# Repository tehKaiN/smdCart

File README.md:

# Custom Sega MegaDrive Cartridges

On this repo you will find schematics for SMD carts of various memory size. Each directory is dedicated to cart of given size.

## Current carts

- `512k` - 512 KByte cart based on 27c4001 chip. Home-etching friendly PCB design. Not tested!
- `1m_29f800` - 1 MByte cart based on 29f800 chip. Erasable/programmable using [ROMprg](https://github.com/tehKaiN/ROMprg) project.
- `2m_29f800` - **Untested!** 1-2 MByte cart based on 1-2 29f800 chips. Erasable/programmable using [ROMprg](https://github.com/tehKaiN/ROMprg) project.

## PCB Ordering instructions

MegaDrive carts have thickness of 1.6mm.

## Creating new cart

When designing PCBs for new cart, the most safe way to get proper dimensions is to copy them from other carts. Some notes:

- maximum cart height is about 60mm, otherwise it won't fit the case;
- distance between mechanical holes is 70mm
- mechanical holes should have diameter of about 6,75mm - add about 1mm for electroplating.
- there should be no soldermask around edge connector pins.

After creating new design and checking if it works, you are encouraged to submit pull request to this repo with your design.

## License

I dunno if MPL2.0 fits hardware, but the idea is that you should share your modifications of schematics / board layout.

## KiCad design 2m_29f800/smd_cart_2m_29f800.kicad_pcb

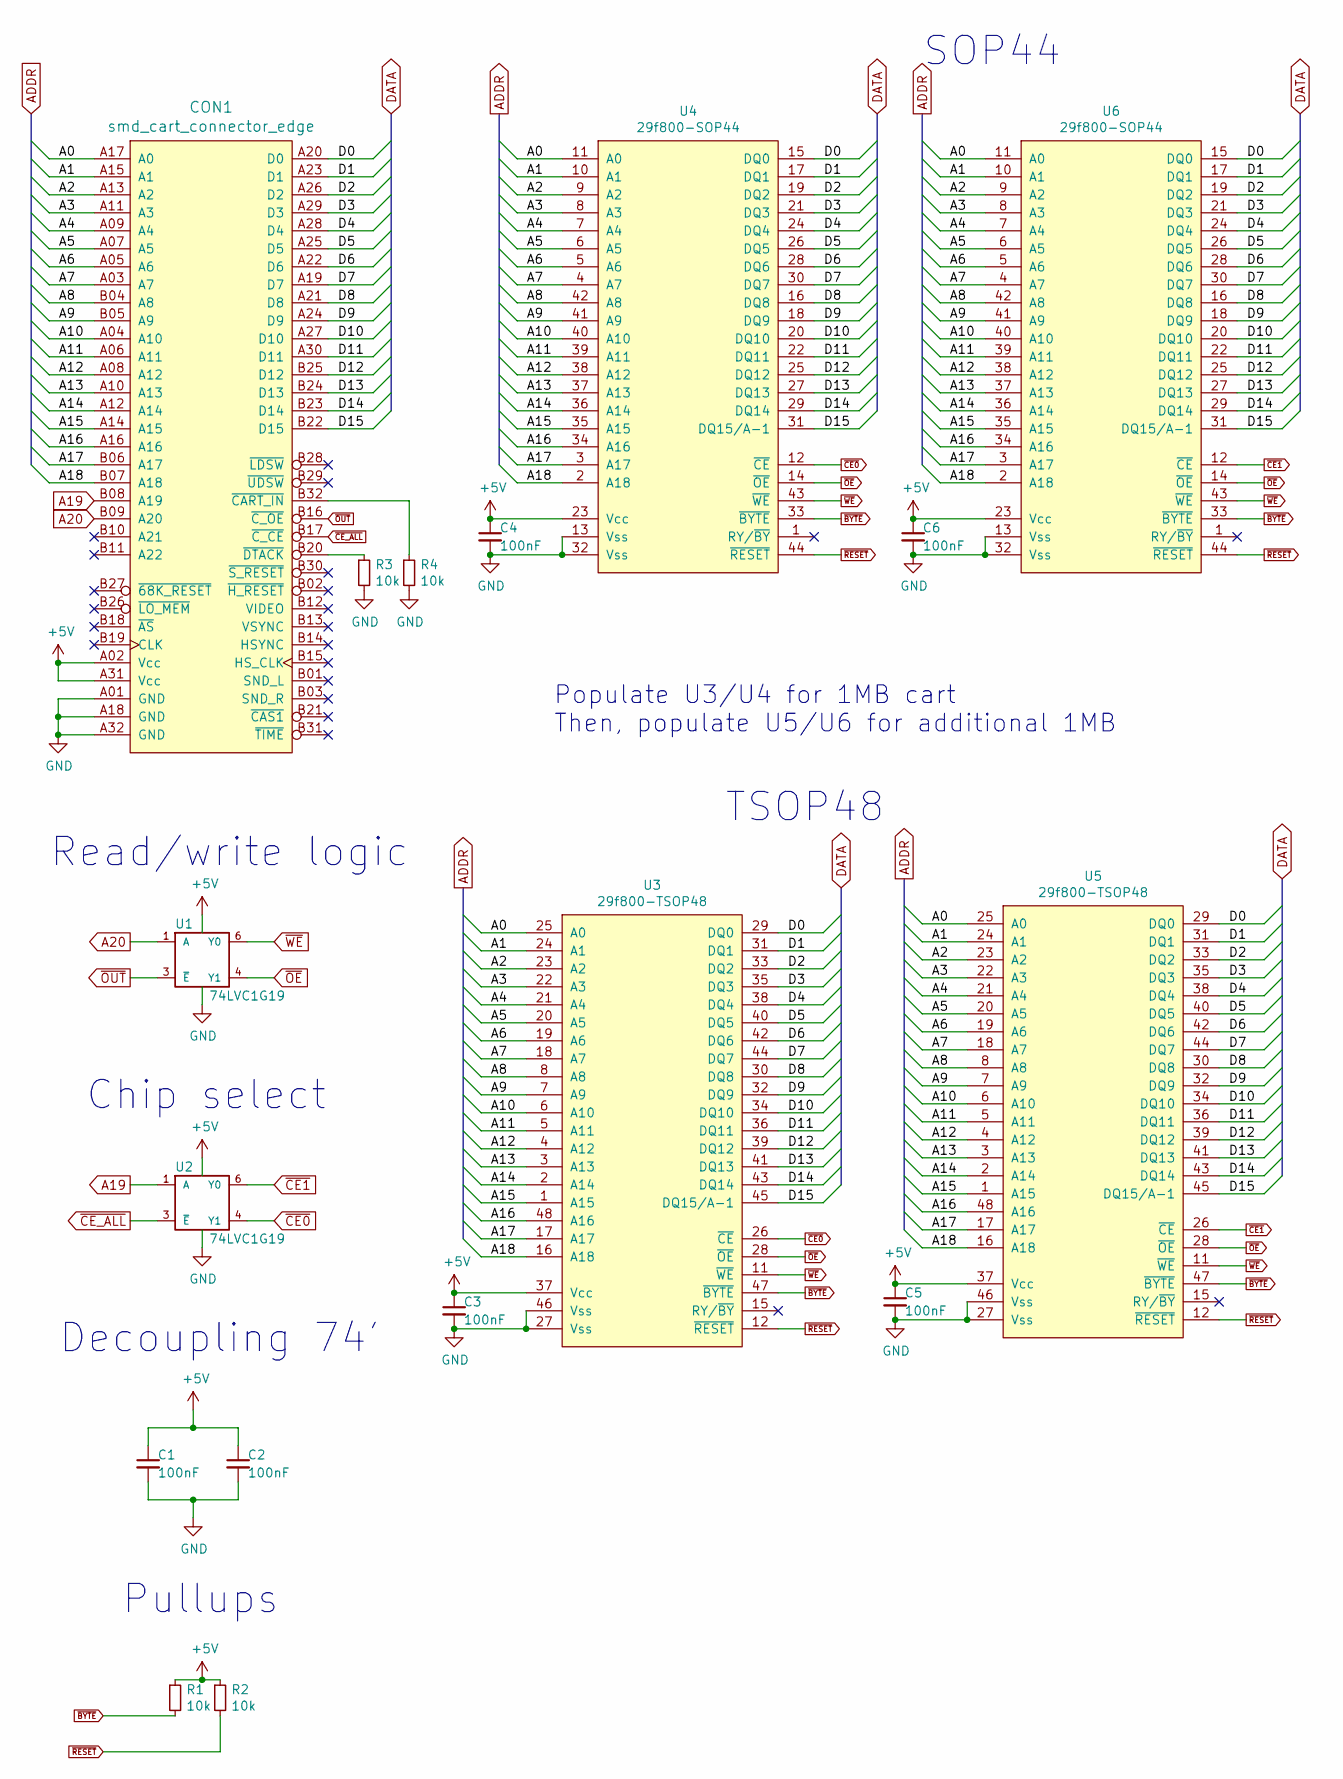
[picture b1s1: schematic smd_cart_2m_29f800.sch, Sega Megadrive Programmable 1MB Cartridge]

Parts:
C1, C2, C3, C4, C5, C6: 100nF; C_0805_2012Metric
CON1: smd_cart_connector_edge; md_cart_edge_conn
R1, R2, R3, R4: 10k; R_0805_2012Metric
U1, U2: 74LVC1G19; SOT-23-6
U3, U5: 29f800-TSOP48; TSOP-I-48_18.4x12mm_P0.5mm
U4, U6: 29f800-SOP44; SOIC-44

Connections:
+5V: C1.1, C2.1, C3.1, C4.1, C5.1, C6.1, CON1.A02 (Vcc), CON1.A31 (Vcc), R1.1, R2.1, U1.5 (VCC), U2.5 (VCC), U3.37 (Vcc), U4.23 (Vcc), U5.37 (Vcc), U6.23 (Vcc)
/A0: CON1.A17 (A0), U3.25 (A0), U4.11 (A0), U5.25 (A0), U6.11 (A0)
/A1: CON1.A15 (A1), U3.24 (A1), U4.10 (A1), U5.24 (A1), U6.10 (A1)
/A2: CON1.A13 (A2), U3.23 (A2), U4.9 (A2), U5.23 (A2), U6.9 (A2)
/A3: CON1.A11 (A3), U3.22 (A3), U4.8 (A3), U5.22 (A3), U6.8 (A3)
/A4: CON1.A09 (A4), U3.21 (A4), U4.7 (A4), U5.21 (A4), U6.7 (A4)
/A5: CON1.A07 (A5), U3.20 (A5), U4.6 (A5), U5.20 (A5), U6.6 (A5)
/A6: CON1.A05 (A6), U3.19 (A6), U4.5 (A6), U5.19 (A6), U6.5 (A6)
/A7: CON1.A03 (A7), U3.18 (A7), U4.4 (A7), U5.18 (A7), U6.4 (A7)
/A8: CON1.B04 (A8), U3.8 (A8), U4.42 (A8), U5.8 (A8), U6.42 (A8)
/A9: CON1.B05 (A9), U3.7 (A9), U4.41 (A9), U5.7 (A9), U6.41 (A9)
/A10: CON1.A04 (A10), U3.6 (A10), U4.40 (A10), U5.6 (A10), U6.40 (A10)
/A11: CON1.A06 (A11), U3.5 (A11), U4.39 (A11), U5.5 (A11), U6.39 (A11)
/A12: CON1.A08 (A12), U3.4 (A12), U4.38 (A12), U5.4 (A12), U6.38 (A12)
/A13: CON1.A10 (A13), U3.3 (A13), U4.37 (A13), U5.3 (A13), U6.37 (A13)
/A14: CON1.A12 (A14), U3.2 (A14), U4.36 (A14), U5.2 (A14), U6.36 (A14)
/A15: CON1.A14 (A15), U3.1 (A15), U4.35 (A15), U5.1 (A15), U6.35 (A15)
/A16: CON1.A16, U3.48 (A16), U4.34 (A16), U5.48 (A16), U6.34 (A16)
/A17: CON1.B06 (A17), U3.17 (A17), U4.3 (A17), U5.17 (A17), U6.3 (A17)
/A18: CON1.B07 (A18), U3.16 (A18), U4.2 (A18), U5.16 (A18), U6.2 (A18)
/D0: CON1.A20 (D0), U3.29 (DQ0), U4.15 (DQ0), U5.29 (DQ0), U6.15 (DQ0)
/D1: CON1.A23 (D1), U3.31 (DQ1), U4.17 (DQ1), U5.31 (DQ1), U6.17 (DQ1)
/D2: CON1.A26 (D2), U3.33 (DQ2), U4.19 (DQ2), U5.33 (DQ2), U6.19 (DQ2)
/D3: CON1.A29 (D3), U3.35 (DQ3), U4.21 (DQ3), U5.35 (DQ3), U6.21 (DQ3)
/D4: CON1.A28 (D4), U3.38 (DQ4), U4.24 (DQ4), U5.38 (DQ4), U6.24 (DQ4)
/D5: CON1.A25 (D5), U3.40 (DQ5), U4.26 (DQ5), U5.40 (DQ5), U6.26 (DQ5)
/D6: CON1.A22 (D6), U3.42 (DQ6), U4.28 (DQ6), U5.42 (DQ6), U6.28 (DQ6)
/D7: CON1.A19 (D7), U3.44 (DQ7), U4.30 (DQ7), U5.44 (DQ7), U6.30 (DQ7)
/D8: CON1.A21 (D8), U3.30 (DQ8), U4.16 (DQ8), U5.30 (DQ8), U6.16 (DQ8)
/D9: CON1.A24 (D9), U3.32 (DQ9), U4.18 (DQ9), U5.32 (DQ9), U6.18 (DQ9)
/D10: CON1.A27 (D10), U3.34 (DQ10), U4.20 (DQ10), U5.34 (DQ10), U6.20 (DQ10)
/D11: CON1.A30 (D11), U3.36 (DQ11), U4.22 (DQ11), U5.36 (DQ11), U6.22 (DQ11)
/D12: CON1.B25 (D12), U3.39 (DQ12), U4.25 (DQ12), U5.39 (DQ12), U6.25 (DQ12)
/D13: CON1.B24 (D13), U3.41 (DQ13), U4.27 (DQ13), U5.41 (DQ13), U6.27 (DQ13)
/D14: CON1.B23 (D14), U3.43 (DQ14), U4.29 (DQ14), U5.43 (DQ14), U6.29 (DQ14)
/D15: CON1.B22 (D15), U3.45 (DQ15/A-1), U4.31 (DQ15/A-1), U5.45 (DQ15/A-1), U6.31 (DQ15/A-1)
A19: CON1.B08 (A19), U2.1 (A)
A20: CON1.B09 (A20), U1.1 (A)
GND: C1.2, C2.2, C3.2, C4.2, C5.2, C6.2, CON1.A01 (GND), CON1.A18 (GND), CON1.A32 (GND), R3.2, R4.2, U1.2 (GND), U2.2 (GND), U3.27 (Vss), U3.46 (Vss), U4.13 (Vss), U4.32 (Vss), U5.27 (Vss), U5.46 (Vss), U6.13 (Vss), U6.32 (Vss)
unnamed: CON1.B20 (~DTACK), R3.1
unnamed: CON1.B32 (~CART_IN), R4.1
~BYTE: R1.2, U3.47 (~BYTE), U4.33 (~BYTE), U5.47 (~BYTE), U6.33 (~BYTE)
~CE0: U2.4 (Y1), U3.26 (~CE), U4.12 (~CE)
~CE1: U2.6 (Y0), U5.26 (~CE), U6.12 (~CE)
~CE_ALL: CON1.B17 (~C_CE), U2.3 (~E)
~OE: U1.4 (Y1), U3.28 (~OE), U4.14 (~OE), U5.28 (~OE), U6.14 (~OE)
~OUT: CON1.B16 (~C_OE), U1.3 (~E)
~RESET: R2.2, U3.12 (~RESET), U4.44 (~RESET), U5.12 (~RESET), U6.44 (~RESET)
~WE: U1.6 (Y0), U3.11 (~WE), U4.43 (~WE), U5.11 (~WE), U6.43 (~WE)

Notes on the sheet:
SOP44
TSOP48
Read/write logic
Decoupling 74'
Chip select
Pullups
Populate U3/U4 for 1MB cart Then, populate U5/U6 for additional 1MB

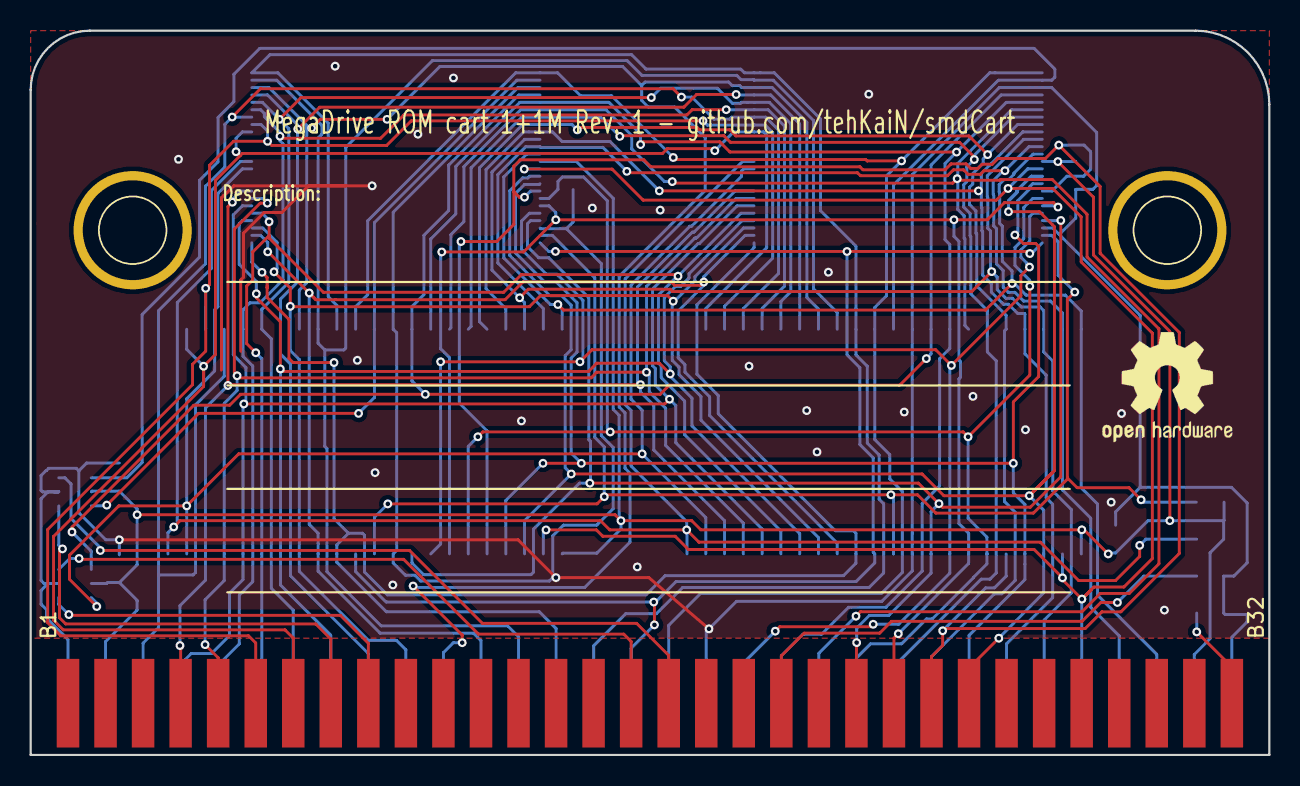
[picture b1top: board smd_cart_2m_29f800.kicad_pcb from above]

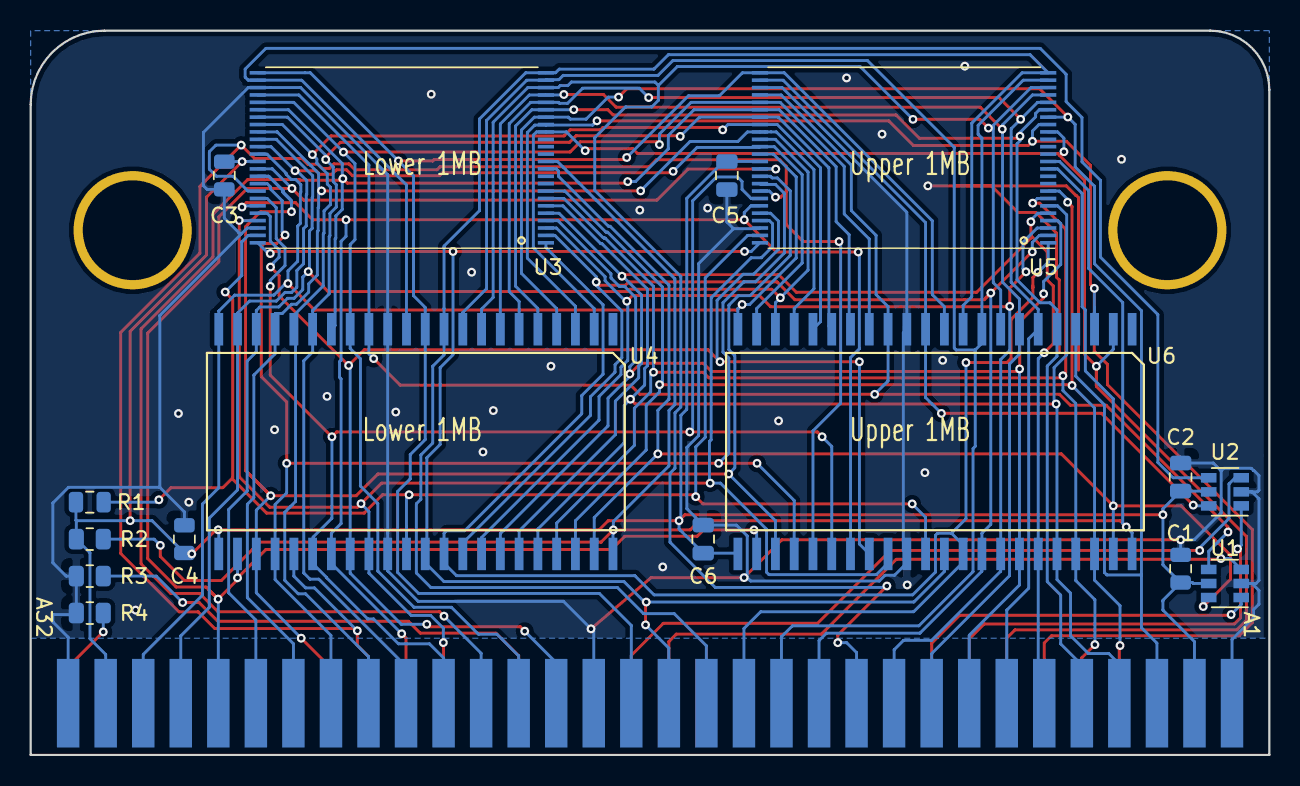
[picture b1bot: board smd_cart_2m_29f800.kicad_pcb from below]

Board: 2 copper layers, 83.8 x 49.0 mm, 19 parts (16 on the bottom side), 49 nets.

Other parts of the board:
DRL1, DRL2: 1pin

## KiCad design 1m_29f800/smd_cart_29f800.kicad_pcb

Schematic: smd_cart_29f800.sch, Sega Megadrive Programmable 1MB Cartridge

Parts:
C1, C2, C3: 100nF; C_0805_2012Metric
CON1: smd_cart_connector_edge; md_cart_edge_conn
R1, R2, R3, R4, R5, R6: 10k; R_0805_2012Metric
U1: 74HCT00; SOIC-14_3.9x8.7mm_P1.27mm
U2: 29f800-TSOP48; TSOP-I-48_18.4x12mm_P0.5mm
U3: 29f800-SOP44; SOIC-44

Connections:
+5V: C1.1, C2.1, C3.1, CON1.A02, CON1.A31, R3.1, R4.1, R5.1, R6.1, U1.14 (VCC), U2.37, U3.23
/A0: CON1.A17, U2.25, U3.11
/A1: CON1.A15, U2.24, U3.10
/A2: CON1.A13, U2.23, U3.9
/A3: CON1.A11, U2.22, U3.8
/A4: CON1.A09, U2.21, U3.7
/A5: CON1.A07, U2.20, U3.6
/A6: CON1.A05, U2.19, U3.5
/A7: CON1.A03, U2.18, U3.4
/A8: CON1.B04, U2.8, U3.42
/A9: CON1.B05, U2.7, U3.41
/A10: CON1.A04, U2.6, U3.40
/A11: CON1.A06, U2.5, U3.39
/A12: CON1.A08, U2.4, U3.38
/A13: CON1.A10, U2.3, U3.37
/A14: CON1.A12, U2.2, U3.36
/A15: CON1.A14, U2.1, U3.35
/A16: CON1.A16, U2.48, U3.34
/A17: CON1.B06, U2.17, U3.3
/A18: CON1.B07, U2.16, U3.2
/D0: CON1.A20, U2.29, U3.15
/D1: CON1.A23, U2.31, U3.17
/D2: CON1.A26, U2.33, U3.19
/D3: CON1.A29, U2.35, U3.21
/D4: CON1.A28, U2.38, U3.24
/D5: CON1.A25, U2.40, U3.26
/D6: CON1.A22, U2.42, U3.28
/D7: CON1.A19, U2.44, U3.30
/D8: CON1.A21, U2.30, U3.16
/D9: CON1.A24, U2.32, U3.18
/D10: CON1.A27, U2.34, U3.20
/D11: CON1.A30, U2.36, U3.22
/D12: CON1.B25, U2.39, U3.25
/D13: CON1.B24, U2.41, U3.27
/D14: CON1.B23, U2.43, U3.29
/D15: CON1.B22, U2.45, U3.31
/OUT: U1.3, U1.5, U1.12
/~A20: U1.8, U1.13
A20: CON1.B09, U1.4, U1.9, U1.10
GND: C1.2, C2.2, C3.2, CON1.A01, CON1.A18, CON1.A32, R1.2, R2.2, U1.7 (GND), U2.27, U2.46, U3.13, U3.32
unnamed: CON1.B20, R1.1
unnamed: CON1.B32, R2.1
unnamed: R3.2, U2.47
unnamed: R4.2, U3.33
unnamed: R5.2, U2.12
unnamed: R6.2, U3.44
~CE: CON1.B17, U2.26, U3.12
~OE: U1.11, U2.28, U3.14
~OUT: CON1.B16, U1.1, U1.2
~WE: U1.6, U2.11, U3.43

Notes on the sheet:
SOP44
TSOP48
Read/write logic
Decoupling

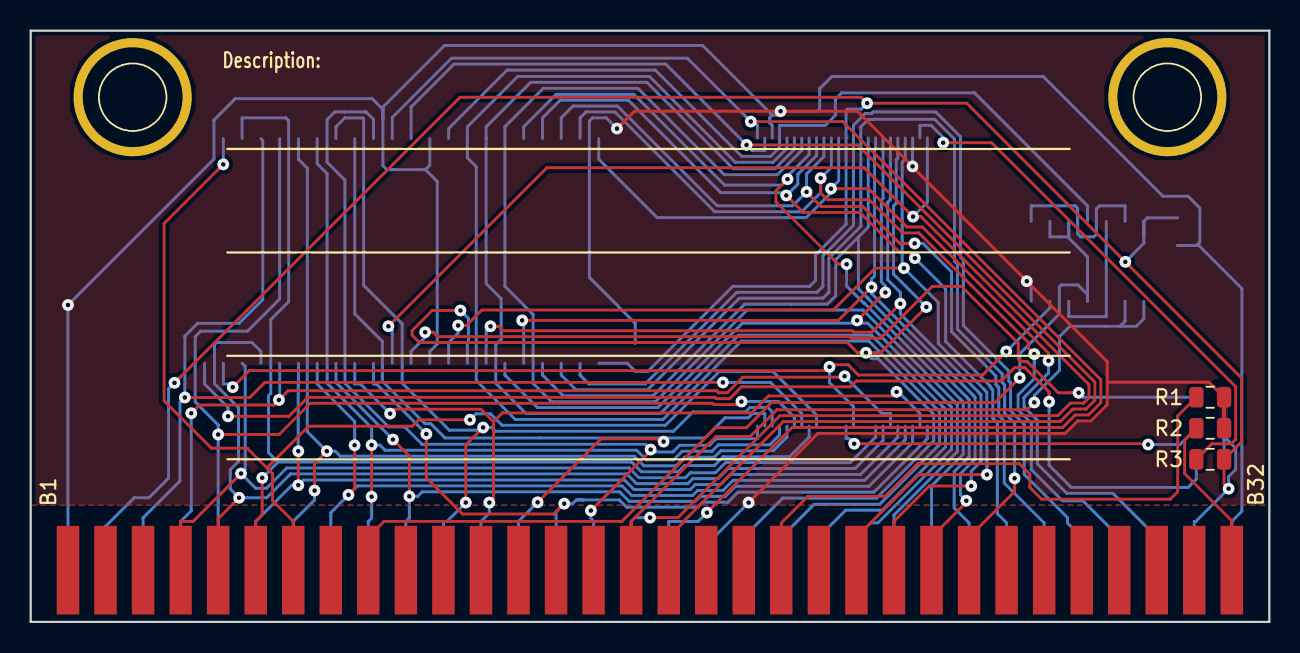
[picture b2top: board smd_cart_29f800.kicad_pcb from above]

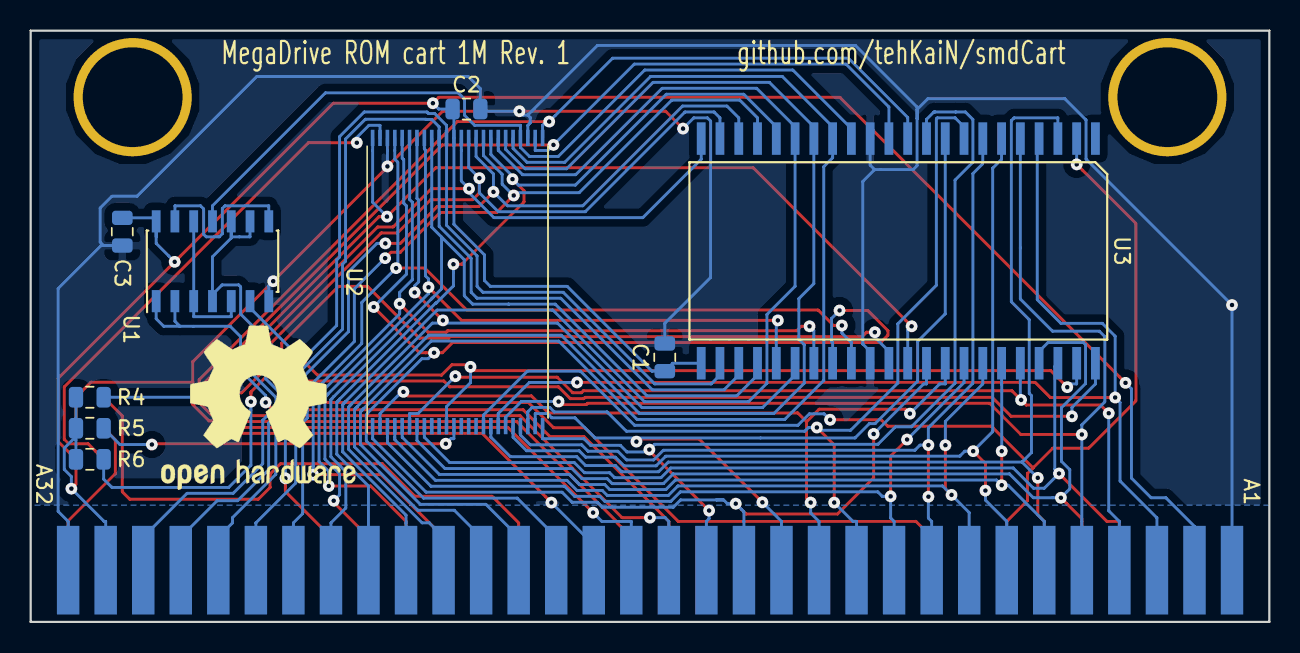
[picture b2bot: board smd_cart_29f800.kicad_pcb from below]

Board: 2 copper layers, 83.8 x 40.0 mm, 15 parts (9 on the bottom side), 50 nets.

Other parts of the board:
DRL1, DRL2: 1pin

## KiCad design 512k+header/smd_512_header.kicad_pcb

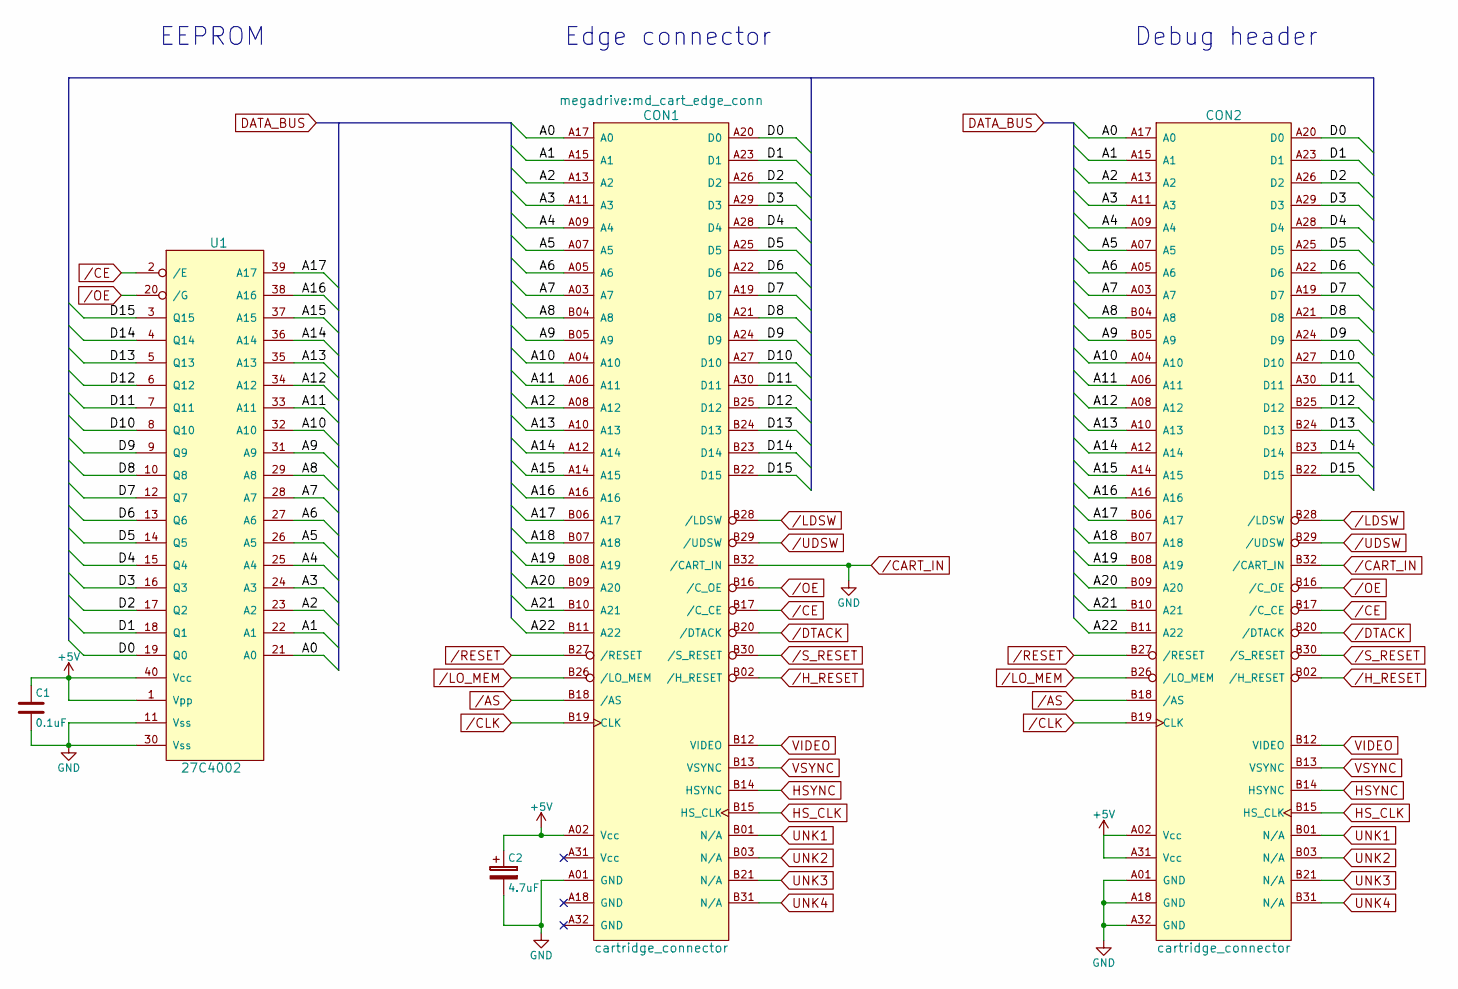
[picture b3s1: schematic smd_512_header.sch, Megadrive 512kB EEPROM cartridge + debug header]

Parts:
C1: 0.1uF; C_0805_HandSoldering
C2: 4.7uF; CP_Radial_D4.0mm_P1.50mm
CON1: cartridge_connector; md_cart_edge_conn
CON2: cartridge_connector; md_cart_edge_conn_desc
U1: 27C4002; DIP-40_W15.24mm_Socket_LongPads

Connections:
+5V: C1.1, C2.1, CON1.A02 (Vcc), CON2.A02 (Vcc), CON2.A31 (Vcc), U1.1 (Vpp), U1.40 (Vcc)
/A0: CON1.A17 (A0), CON2.A17 (A0), U1.21 (A0)
/A1: CON1.A15 (A1), CON2.A15 (A1), U1.22 (A1)
/A2: CON1.A13 (A2), CON2.A13 (A2), U1.23 (A2)
/A3: CON1.A11 (A3), CON2.A11 (A3), U1.24 (A3)
/A4: CON1.A09 (A4), CON2.A09 (A4), U1.25 (A4)
/A5: CON1.A07 (A5), CON2.A07 (A5), U1.26 (A5)
/A6: CON1.A05 (A6), CON2.A05 (A6), U1.27 (A6)
/A7: CON1.A03 (A7), CON2.A03 (A7), U1.28 (A7)
/A8: CON1.B04 (A8), CON2.B04 (A8), U1.29 (A8)
/A9: CON1.B05 (A9), CON2.B05 (A9), U1.31 (A9)
/A10: CON1.A04 (A10), CON2.A04 (A10), U1.32 (A10)
/A11: CON1.A06 (A11), CON2.A06 (A11), U1.33 (A11)
/A12: CON1.A08 (A12), CON2.A08 (A12), U1.34 (A12)
/A13: CON1.A10 (A13), CON2.A10 (A13), U1.35 (A13)
/A14: CON1.A12 (A14), CON2.A12 (A14), U1.36 (A14)
/A15: CON1.A14 (A15), CON2.A14 (A15), U1.37 (A15)
/A16: CON1.A16, CON2.A16, U1.38 (A16)
/A17: CON1.B06 (A17), CON2.B06 (A17), U1.39 (A17)
/A18: CON1.B07 (A18), CON2.B07 (A18)
/A19: CON1.B08 (A19), CON2.B08 (A19)
/A20: CON1.B09 (A20), CON2.B09 (A20)
/A21: CON1.B10 (A21), CON2.B10 (A21)
/A22: CON1.B11 (A22), CON2.B11 (A22)
/AS: CON1.B18 (/AS), CON2.B18 (/AS)
/CART_IN: C1.2, C2.2, CON1.A01 (GND), CON1.B32 (/CART_IN), CON2.A01 (GND), CON2.A18 (GND), CON2.A32 (GND), CON2.B32 (/CART_IN), U1.11 (Vss), U1.30 (Vss)
/CE: CON1.B17 (/C_CE), CON2.B17 (/C_CE), U1.2 (/E)
/CLK: CON1.B19 (CLK), CON2.B19 (CLK)
/D0: CON1.A20 (D0), CON2.A20 (D0), U1.19 (Q0)
/D1: CON1.A23 (D1), CON2.A23 (D1), U1.18 (Q1)
/D2: CON1.A26 (D2), CON2.A26 (D2), U1.17 (Q2)
/D3: CON1.A29 (D3), CON2.A29 (D3), U1.16 (Q3)
/D4: CON1.A28 (D4), CON2.A28 (D4), U1.15 (Q4)
/D5: CON1.A25 (D5), CON2.A25 (D5), U1.14 (Q5)
/D6: CON1.A22 (D6), CON2.A22 (D6), U1.13 (Q6)
/D7: CON1.A19 (D7), CON2.A19 (D7), U1.12 (Q7)
/D8: CON1.A21 (D8), CON2.A21 (D8), U1.10 (Q8)
/D9: CON1.A24 (D9), CON2.A24 (D9), U1.9 (Q9)
/D10: CON1.A27 (D10), CON2.A27 (D10), U1.8 (Q10)
/D11: CON1.A30 (D11), CON2.A30 (D11), U1.7 (Q11)
/D12: CON1.B25 (D12), CON2.B25 (D12), U1.6 (Q12)
/D13: CON1.B24 (D13), CON2.B24 (D13), U1.5 (Q13)
/D14: CON1.B23 (D14), CON2.B23 (D14), U1.4 (Q14)
/D15: CON1.B22 (D15), CON2.B22 (D15), U1.3 (Q15)
/DTACK: CON1.B20 (/DTACK), CON2.B20 (/DTACK)
/H_RESET: CON1.B02 (/H_RESET), CON2.B02 (/H_RESET)
/LDSW: CON1.B28 (/LDSW), CON2.B28 (/LDSW)
/LO_MEM: CON1.B26 (/LO_MEM), CON2.B26 (/LO_MEM)
/OE: CON1.B16 (/C_OE), CON2.B16 (/C_OE), U1.20 (/G)
/RESET: CON1.B27 (/RESET), CON2.B27 (/RESET)
/S_RESET: CON1.B30 (/S_RESET), CON2.B30 (/S_RESET)
/UDSW: CON1.B29 (/UDSW), CON2.B29 (/UDSW)
HSYNC: CON1.B14 (HSYNC), CON2.B14 (HSYNC)
HS_CLK: CON1.B15 (HS_CLK), CON2.B15 (HS_CLK)
UNK1: CON1.B01 (N/A), CON2.B01 (N/A)
UNK2: CON1.B03 (N/A), CON2.B03 (N/A)
UNK3: CON1.B21 (N/A), CON2.B21 (N/A)
UNK4: CON1.B31 (N/A), CON2.B31 (N/A)
VIDEO: CON1.B12 (VIDEO), CON2.B12 (VIDEO)
VSYNC: CON1.B13 (VSYNC), CON2.B13 (VSYNC)

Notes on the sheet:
Edge connector
EEPROM
Debug header

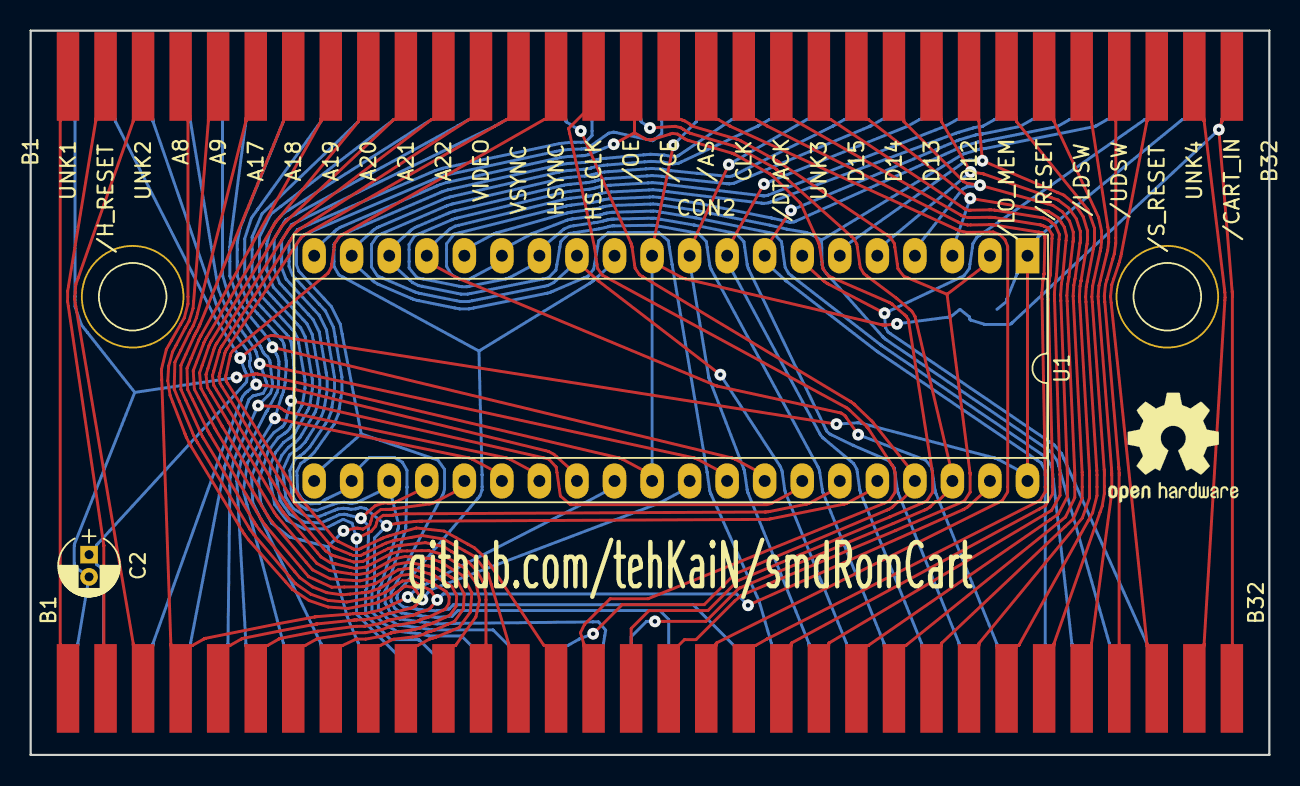
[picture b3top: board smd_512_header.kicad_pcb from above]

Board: 2 copper layers, 83.8 x 49.0 mm, 8 parts (1 on the bottom side), 60 nets.

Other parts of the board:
DRL1, DRL2: 1pin
LOGO2: OSHW-Logo2_9.8x8mm_SilkScreen

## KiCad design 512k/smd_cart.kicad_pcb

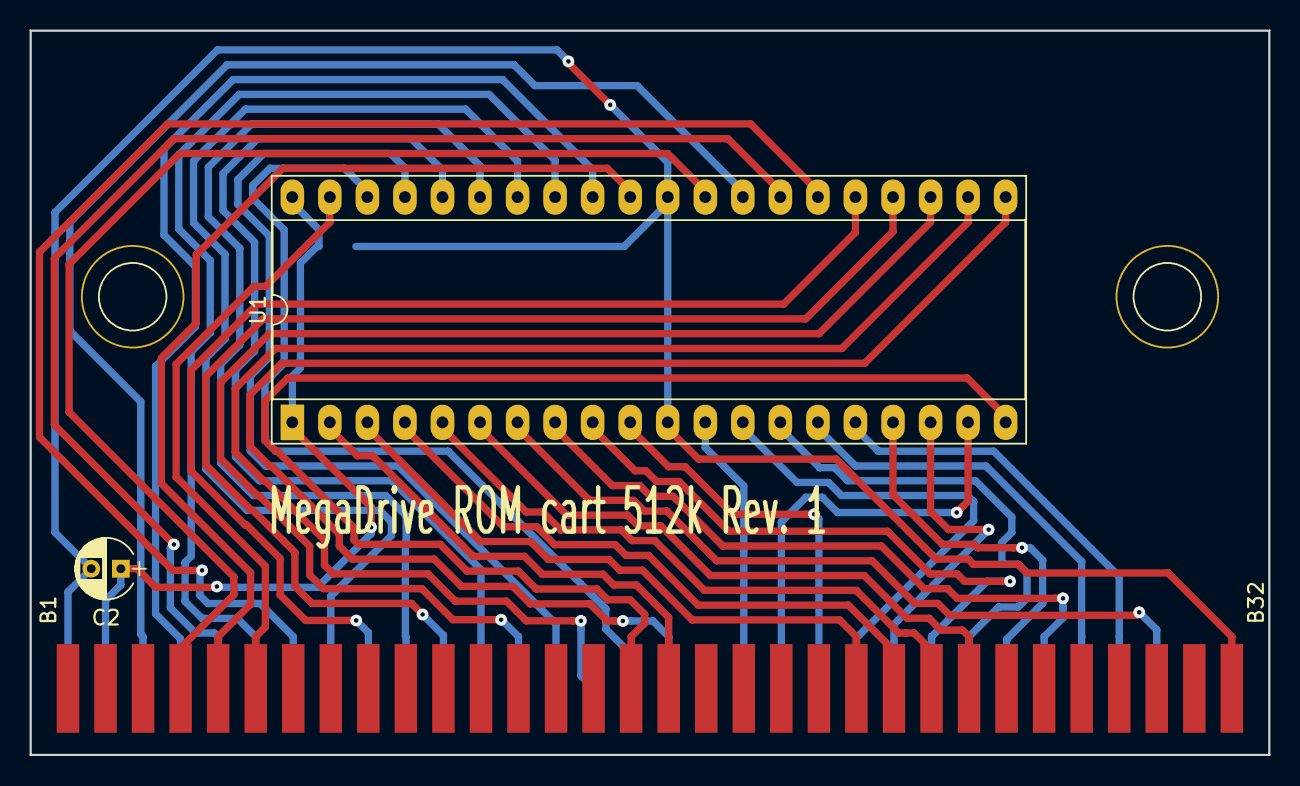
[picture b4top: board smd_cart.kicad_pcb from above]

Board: 2 copper layers, 83.8 x 49.0 mm, 4 parts (1 on the bottom side), 38 nets.

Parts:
C1: 0.1uF; C_0805_HandSoldering
C2: 4.7uF; CP_Radial_D4.0mm_P2.00mm
CON1: cartridge_connector; md_cart_edge_conn
U1: 27C4002; DIP-40_W15.24mm_Socket_LongPads

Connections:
+5V: C1.1, C2.1, CON1.A02, U1.1, U1.40
/A0: CON1.A17, U1.21
/A1: CON1.A15, U1.22
/A2: CON1.A13, U1.23
/A3: CON1.A11, U1.24
/A4: CON1.A09, U1.25
/A5: CON1.A07, U1.26
/A6: CON1.A05, U1.27
/A7: CON1.A03, U1.28
/A8: CON1.B04, U1.29
/A9: CON1.B05, U1.31
/A10: CON1.A04, U1.32
/A11: CON1.A06, U1.33
/A12: CON1.A08, U1.34
/A13: CON1.A10, U1.35
/A14: CON1.A12, U1.36
/A15: CON1.A14, U1.37
/A16: CON1.A16, U1.38
/A17: CON1.B06, U1.39
/CE: CON1.B17, U1.2
/D0: CON1.A20, U1.19
/D1: CON1.A23, U1.18
/D2: CON1.A26, U1.17
/D3: CON1.A29, U1.16
/D4: CON1.A28, U1.15
/D5: CON1.A25, U1.14
/D6: CON1.A22, U1.13
/D7: CON1.A19, U1.12
/D8: CON1.A21, U1.10
/D9: CON1.A24, U1.9
/D10: CON1.A27, U1.8
/D11: CON1.A30, U1.7
/D12: CON1.B25, U1.6
/D13: CON1.B24, U1.5
/D14: CON1.B23, U1.4
/D15: CON1.B22, U1.3
/OE: CON1.B16, U1.20
GND: C1.2, C2.2, CON1.A01, CON1.B32, U1.11, U1.30

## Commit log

2017-11-01 Added 512k cartridge
2017-11-01 added proper readme
2018-03-04 Moved libs to separate directory
2018-03-06 Added edge connector with description & pin-variant
2018-03-06 Added 512k cart with debug header
2018-03-06 Added 2 missing pin descriptions on footprint md_cart_endge_conn_desc
2018-09-09 Updated cart connector symbols, added slot symbol
2018-09-10 Added footprint for cartridge slot
2018-09-11 Added 29f800 symbols
2018-09-11 changed license to MPL2.0
2018-09-11 Initial routing of 29f800 cart, could be done better
2021-06-22 fixed library paths
2021-06-22 added license note
2021-06-28 added 2MB experimental cart
